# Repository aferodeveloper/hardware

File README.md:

## Afero ASR-1 Secure Radio Module Library ##

- **ASR-1 library files** provided in Allegro, Eagle, and OrCad Capture file formats.

## Afero Module Development Board ##

- **Modulo layout** in Allegro 16.6 file format.
- **Modulo schematic** in Orcad Capture file format.

## Afero Plinto Development Board ##

- **Plinto layout** in Eagle file format.
- **Plinto schematic** in Eagle file format.

### More Information ###

<http://developer.afero.io>

### License ###

Copyright 2015 Afero, Inc.

Licensed under the Creative Commons Attribution 4.0 International Public 
License (the "License"); you may not use this file except in compliance 
with the License. You may obtain a copy of the License at:

<http://creativecommons.org/licenses/by/4.0/legalcode>

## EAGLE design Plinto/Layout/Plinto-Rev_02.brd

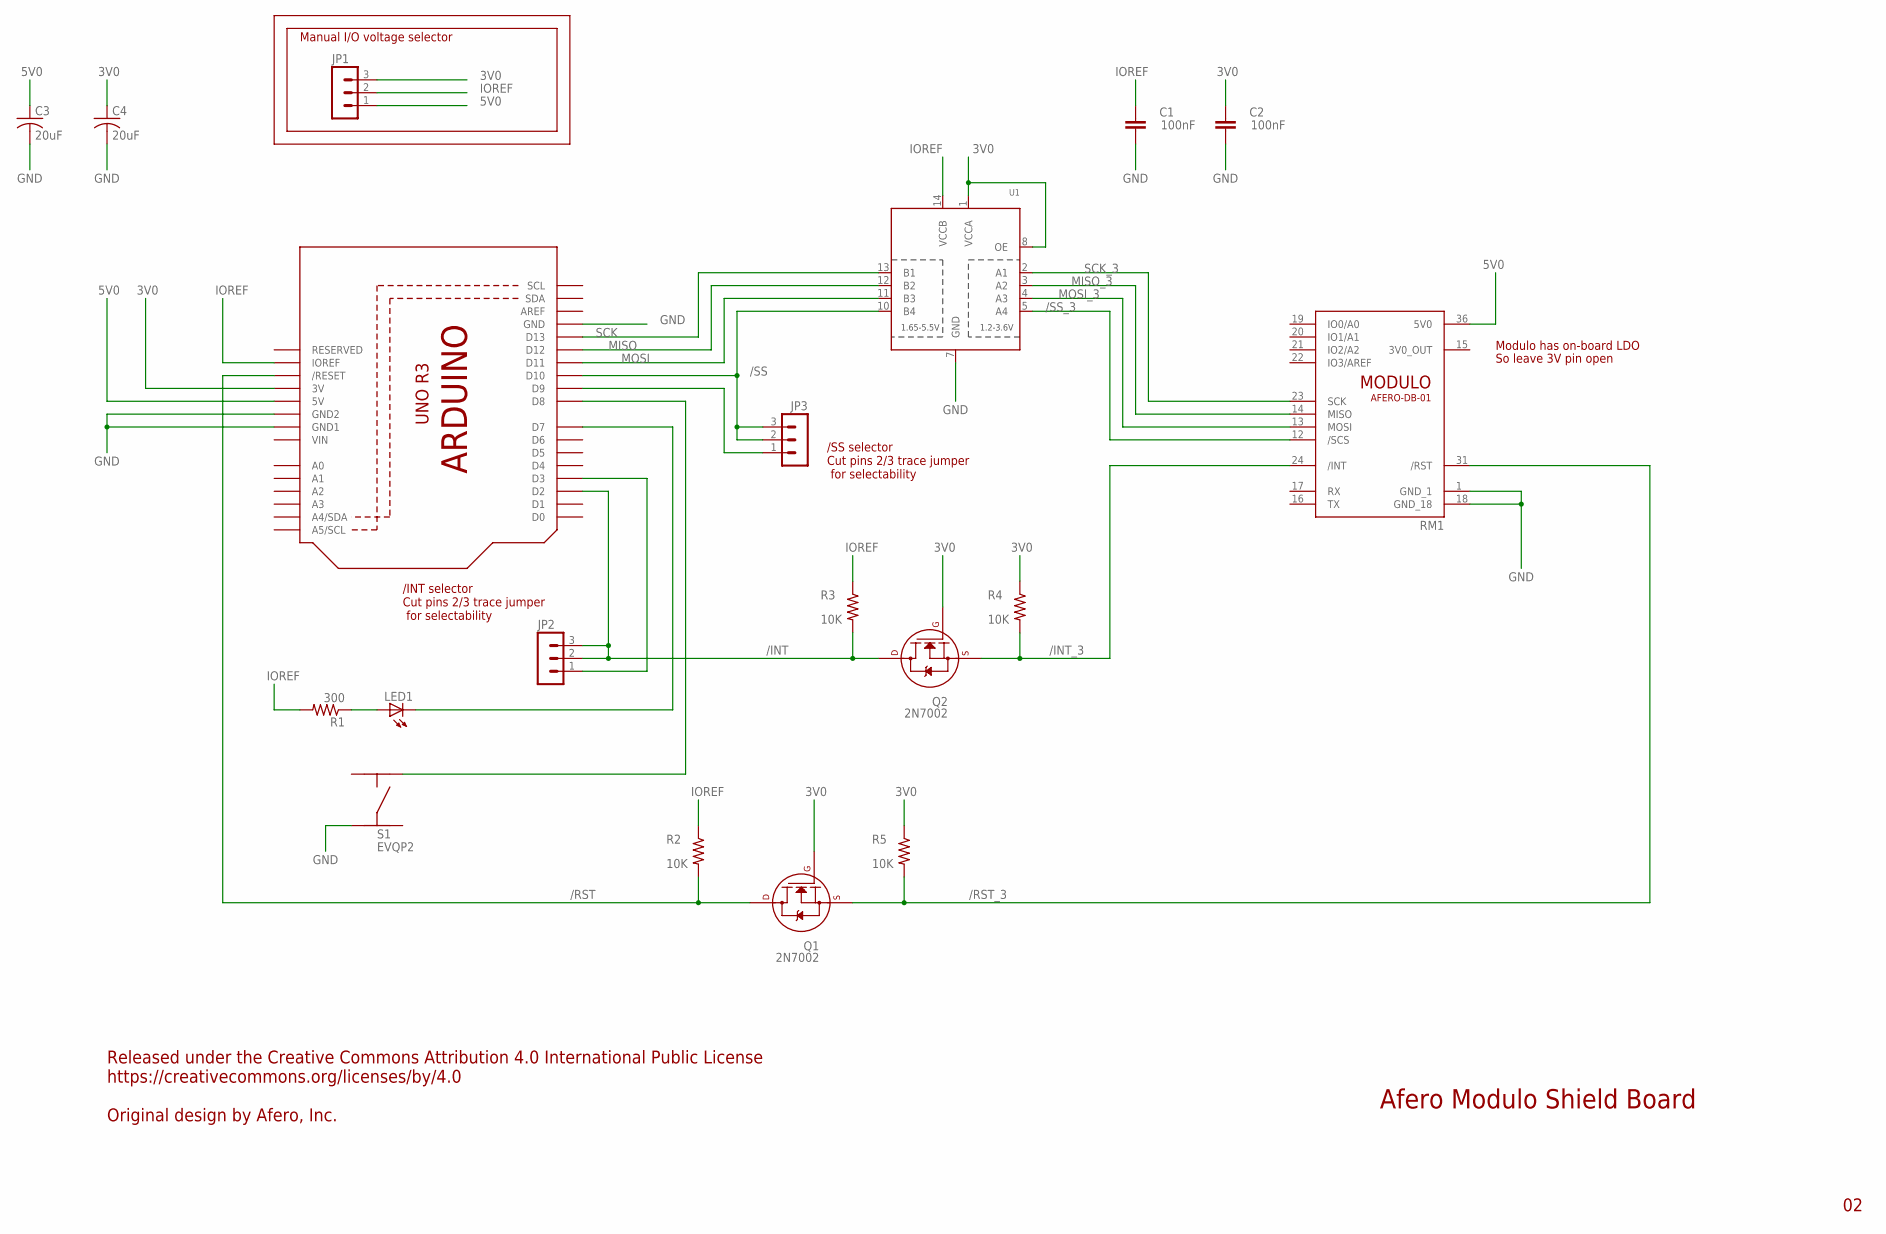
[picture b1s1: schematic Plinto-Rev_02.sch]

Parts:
C1, C2: 100nF; C0402
C3, C4: 20uF; C0805
JP1, JP2, JP3: 3PIN_JMPR
LED1: LEDCHIPLED_0603; CHIPLED_0603
Q1, Q2: 2N7002; SOT-23
R1: 300; R0402
R2, R3, R4, R5: 10K; R0402
RM1: MODULOAFERO-DB-01; MODULO
S1: EVQP2
U1: TXB0104PWR; TSSOP14
U$1: ARDUINO_UNO_R3KIBANVERSION; ARDUINO_R3

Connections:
3V0: C2.1, C4.1, JP1.3, Q1.1 (G), Q2.1 (G), R4.1, R5.1, U1.1 (VCCA), U1.8 (OE), U$1.3V
3V0_OUT: RM1.15 (3V0_OUT)
5V0: C3.1, JP1.1, RM1.36 (5V0), U$1.5V
/INT: JP2.2, JP2.3, Q2.3 (D), R3.2, U$1.D2
/INT_3: Q2.2 (S), R4.2, RM1.24 (/INT)
/RST: Q1.3 (D), R2.2, U$1.RESET (/RESET)
/RST_3: Q1.2 (S), R5.2, RM1.31 (/RST)
/SS: JP3.2, JP3.3, U1.10 (B4), U$1.D10
/SS_3: RM1.12 (/SCS), U1.5 (A4)
GND: C1.2, C2.2, C3.2, C4.2, RM1.1 (GND_1), RM1.18 (GND_18), S1.P$4, U1.7 (GND), U$1.GND, U$1.GND1, U$1.GND2
IOREF: C1.1, JP1.2, R1.2, R2.1, R3.1, U1.14 (VCCB), U$1.IOREF
MISO: U1.12 (B2), U$1.D12
MISO_3: RM1.14 (MISO), U1.3 (A2)
MOSI: U1.11 (B3), U$1.D11
MOSI_3: RM1.13 (MOSI), U1.4 (A3)
unnamed: LED1.A, R1.1
unnamed: LED1.C, U$1.D7
unnamed: JP2.1, U$1.D3
unnamed: S1.P$1, U$1.D8
unnamed: JP3.1, U$1.D9
SCK: U1.13 (B1), U$1.D13
SCK_3: RM1.23 (SCK), U1.2 (A1)
VIN: U$1.VIN

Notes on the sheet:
Manual I/O voltage selector
Modulo has on-board LDO
So leave 3V pin open
/INT selector Cut pins 2/3 trace jumper for selectability
Released under the Creative Commons Attribution 4.0 International Public License https://creativecommons.org/licenses/by/4.0 Original design by Afero, Inc.
/SS selector Cut pins 2/3 trace jumper for selectability
Afero Modulo Shield Board

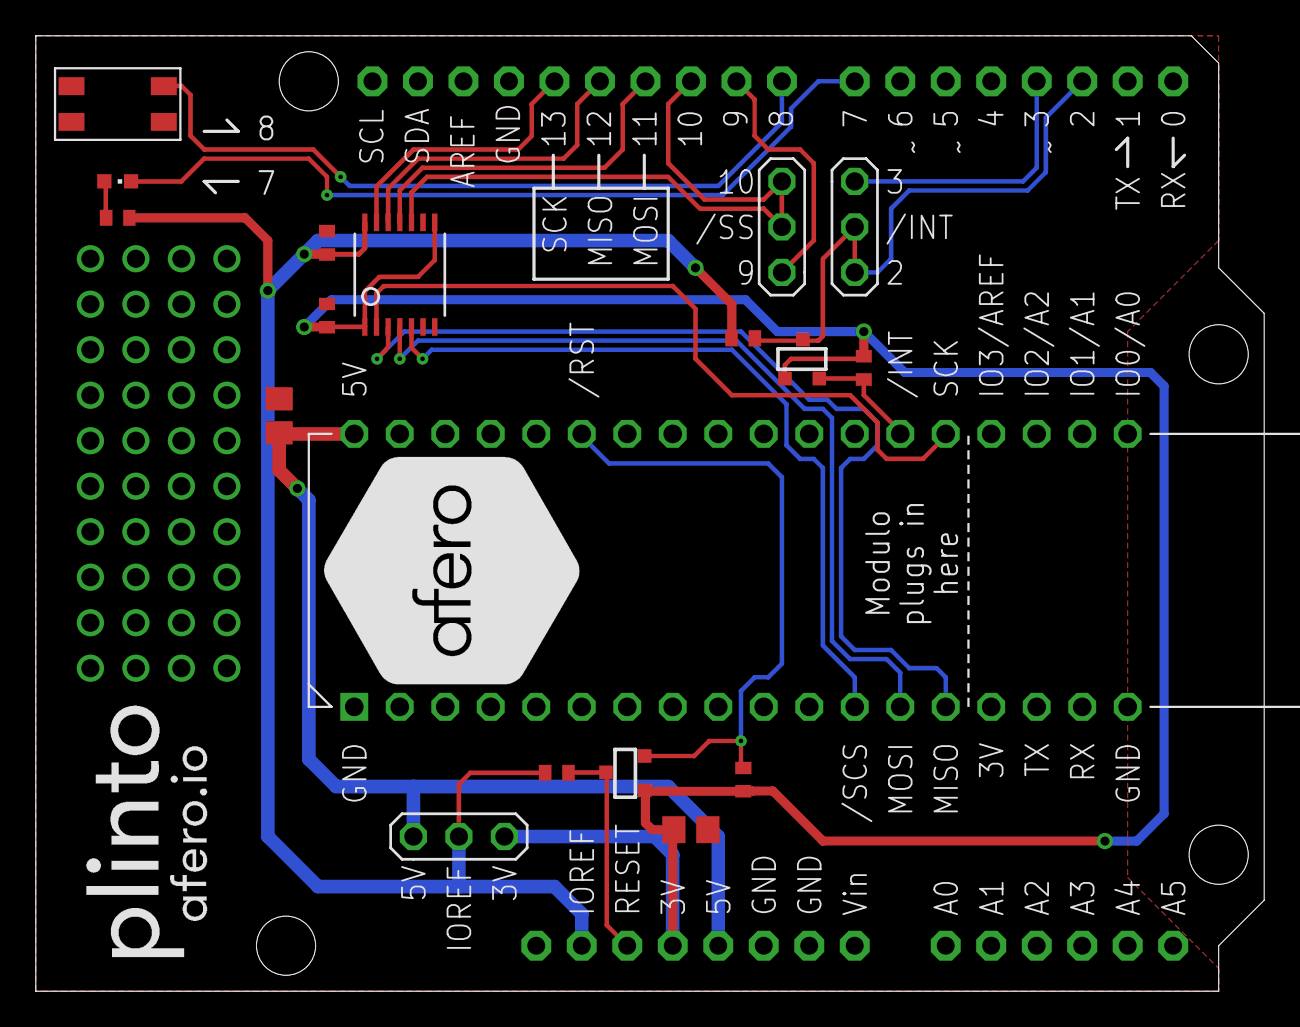
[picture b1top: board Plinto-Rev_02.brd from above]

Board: 2 copper layers, 68.6 x 53.3 mm, 20 parts (0 on the bottom side), 21 nets.

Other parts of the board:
U$2: AFERO_LOGO_SMALL

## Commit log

2015-12-11 Update LICENSE
2015-12-15 Initial checkin of Afero hardware files.
2016-05-16 Add Modulo schematic in PDF format for reference
2016-05-16 update board files to rev_04
2023-02-27 automation testing
